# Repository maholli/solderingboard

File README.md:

# solderingboard
Solder qualification board for hands-on portion of https://sites.google.com/stanford.edu/soldering-internal/learning

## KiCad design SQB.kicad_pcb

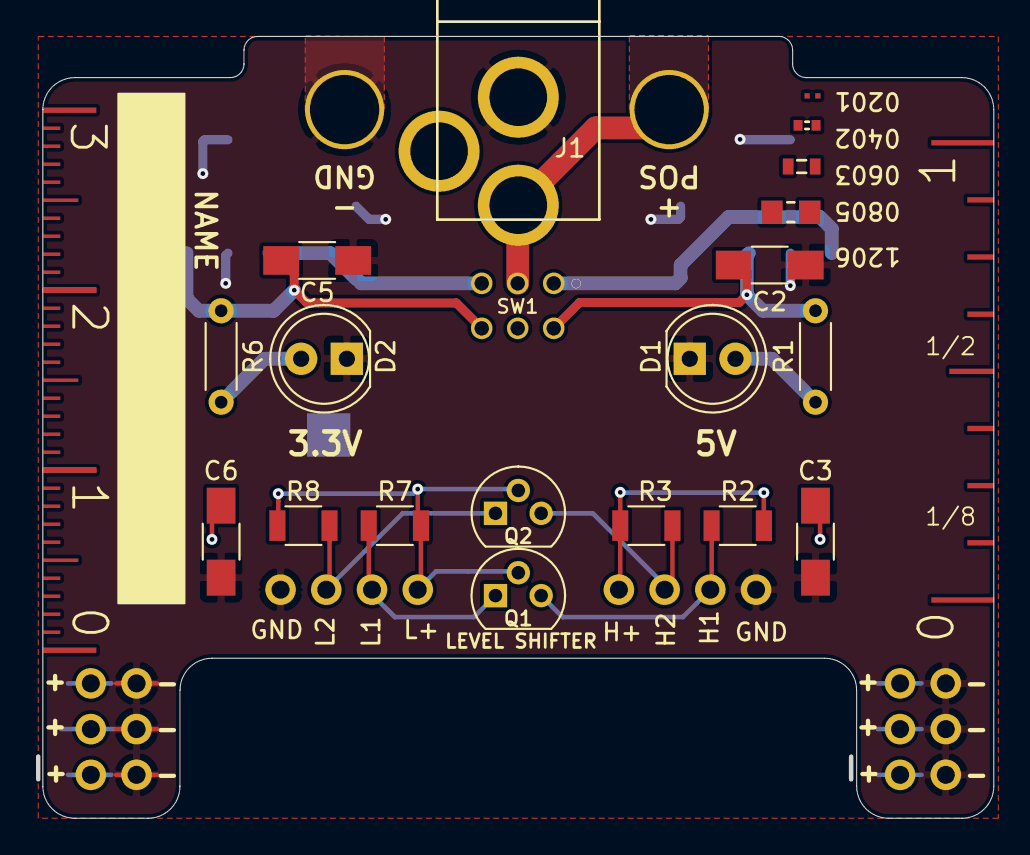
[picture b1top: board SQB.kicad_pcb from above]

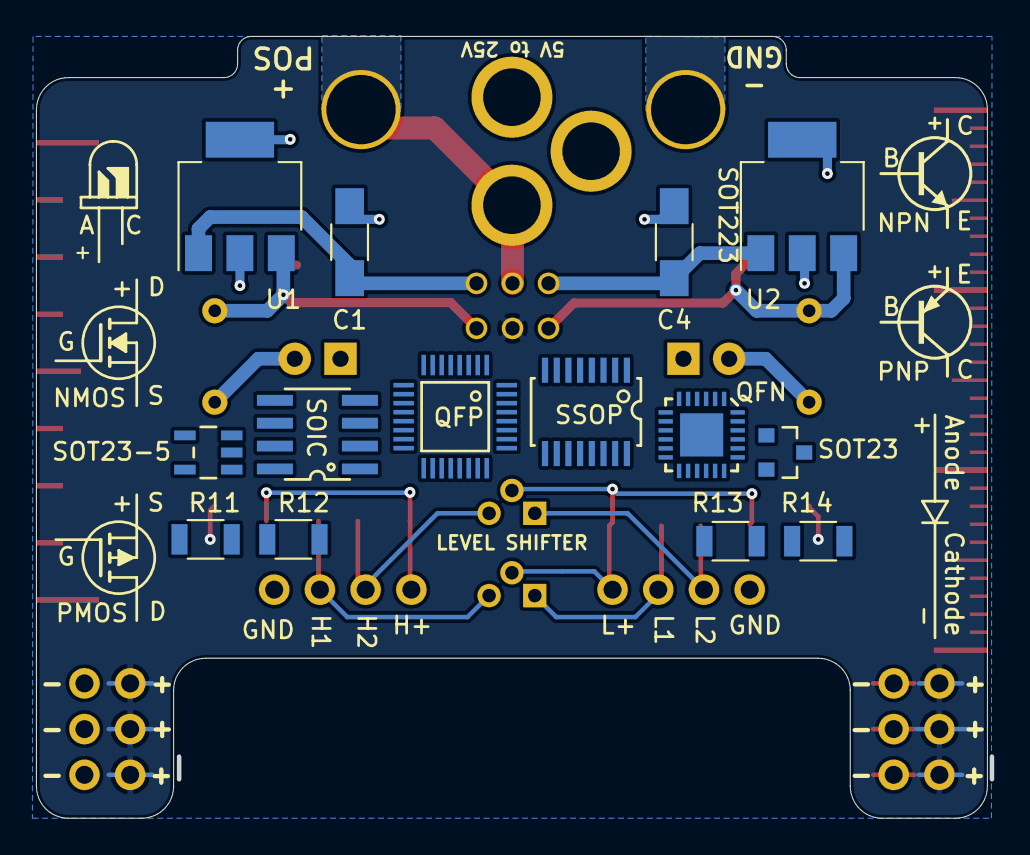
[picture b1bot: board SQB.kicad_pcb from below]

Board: 2 copper layers, 53.0 x 43.2 mm, 50 parts (20 on the bottom side), 15 nets.

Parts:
C1, C4: 0.22uF; C_1206_HandSoldering
C2, C3, C5, C6: 0.1uF; C_1206_HandSoldering
D1, D2: LED; LED_D5.0mm
E$3, E$4, E$5: EDGE-MILLIMETERS
E$18: EDGE-INCHES-EIGTH
E$25: 0805
E$33: SOT23-5
E$34: SOT23-3
E$50: NMOS-SYMB
E$51: PMOS-SYMB
E$52: DIODE-SYMB
E$53: LED-GUIDE
E$54: NPN-SYMB
E$55: QFN-24
E$56: TSSOP16
E$57: SO08
E$58: TQFP32-5MM
E$59: PNP-SYMB
E$60: 0201
E$61: 0402
E$62: 0603
H1, H2: MountingHole_Pad; MountingHole_2.2mm_M2_Pad
J1: Barrel_Jack; BARREL_JACK
J2, J3: Conn_02x04_Odd_Even; PinHeader_2x04_P2.54mm_Vertical
J4, J5: Conn_01x04; Pin_Header_Straight_1x04_Pitch2.54mm
Q1, Q2: Q_NMOS_SGD; TO-92
R1, R6: 330; R_Axial_DIN0204_L3.6mm_D1.6mm_P5.08mm_Horizontal
R2, R3, R7, R8, R11, R12, R13, R14: 10k; R_1206
SW1: EG2209A; EG2209
U1: LM340; SOT-223-3_TabPin2
U2: LM2937; SOT-223-3_TabPin2

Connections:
/VOUT: C3.2, C6.2, J2.3, J2.5, J2.7, J3.3, J3.5, J3.7, SW1.5
GND: C1.2, C2.2, C3.1, C4.2, C5.2, C6.1, D1.1, D2.1, H2.1, J1.2, J2.4, J2.6, J2.8, J3.4, J3.6, J3.8, J4.4, J5.4, U1.2, U2.2
HIGH: J4.1, R2.1, R3.1
HIGH_1: J4.3, Q1.3, R2.2
HIGH_2: J4.2, Q2.3, R3.2
LOW: J5.1, Q1.2, Q2.2, R7.1, R8.1
LOW_1: J5.2, Q1.1, R7.2
LOW_2: J5.3, Q2.1, R8.2
unnamed: C1.1, SW1.1, U1.1
unnamed: C2.1, R1.2, SW1.4, U1.3
unnamed: C4.1, SW1.3, U2.1
unnamed: C5.1, R6.1, SW1.6, U2.3
unnamed: D1.2, R1.1
unnamed: D2.2, R6.2
VCC: H1.1, J1.1, SW1.2

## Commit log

2019-07-23 adding v01b single board files (not panelized!)
2019-07-23 adding schematic pdf
